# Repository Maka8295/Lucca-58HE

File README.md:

# Lucca 58HE
The Lucca 58HE is a 58 key hall effect split keyboard!

This keyboard is still very much a work in progress!! Kicad files for PCBs and switch plate, 3d files for case all available. Currently working under KMK!

## Features

- Fully addressable per-key RGB
- 10-point RGB Underglow on each half
- Full USB-C support
- Hardware support for both SPI and UART communication between halves
- OLED screens
- Rapid Trigger
- 3D Printed Case
- Compatible with standard HE Switches, I reccomend Gateron Jades

## Bill of Materials

- Multiplexer - ADG732BSUZ 
- MCU - Waveshare RP2040 Zero 
- OLED - SSD1306 128x32 
- HE Sensor - DRV5053VAQDBZR 
- LPF Resistor 1.5k Ohm 0805 package
- I2C / SPI pull-up resistor 4.7k Ohm 0805 package
- 0 Ohm Resistors for UART mode 0805 package
- Filter caps 100nF 0805 package
- SK6803 MINI-E (you can use SK6812 instead but dont use both under glow and per key as current draw is too high)
- M2.5, 3mm brass stand offs 
- M2.5, 12mm screws with flat tops
- M2.5 x 6 x 0.4mm washers 
- M2.5 nuts 1.8mm thick
- My 3d Printed case!

## How To Install

- ...

## To do

- OLED code implementation
- implement auto calibration
- QMK port
- New HE sensor?

NEW STATUS UPDATE:

Am currently typing this update from the Lucca58HE! So its fully up and running now! There is definitely a slight latency with UART on the slave half of the keyboard. The PCB supports SPI which could potentialy have latency reductions. It might also be possible to get UART latency down too, especially once im using QMK.

OLD STATUS UPDATES:

Left half of the keyboard is now perfectly functioning under KMK! changing the actuation from from 0 to 3.5mm is possible, but some weirdness means theres a deadzone towards the end of the keystroke, it can be fixed by increasing the distance between the switch plate and PCB so not a big deal. Could probably be avoided with different HE sensors?

Working with QMK has proved a lot more difficult than i thought, so im going to get it working with KMK and circuitpython first, and then worry about QMK support after!

Hall effect sensors are currently resulting in a resolution of 0.00706mm, so things are looking very promising. My choice of HE sensor results in a voltage range of ~0 to ~0.4v, so using a different HE sensor with a greater sensitivity (not to be confused with resolution) could result in even greater resolution of distance traveled, as the 12bit ADC on the RP2040 references the internal 3.3v. Am going on family holiday soon so progress will slow down a lot, may not be able to finish the project until the new year...

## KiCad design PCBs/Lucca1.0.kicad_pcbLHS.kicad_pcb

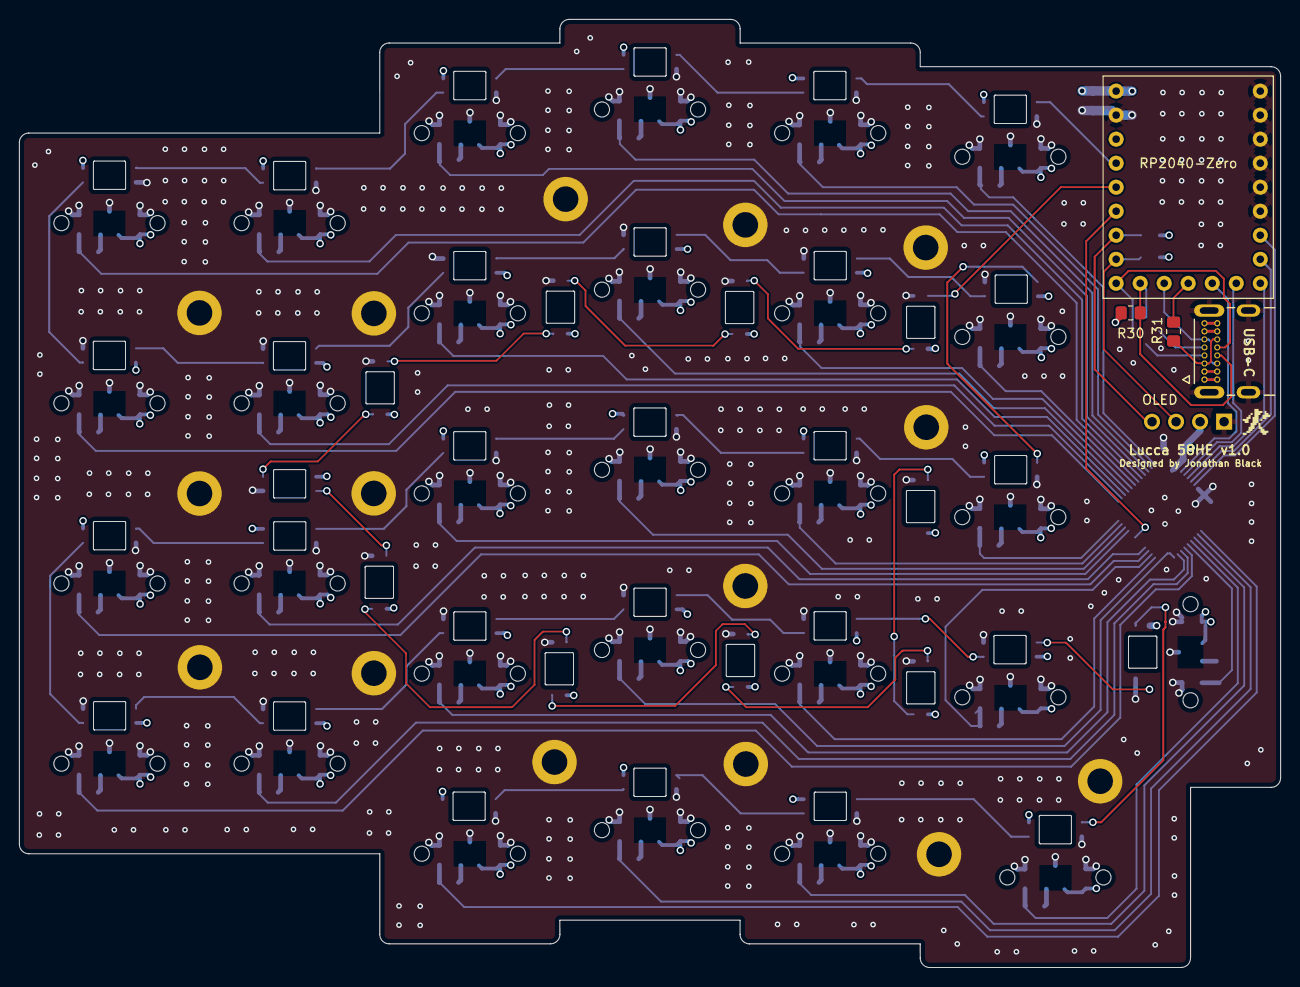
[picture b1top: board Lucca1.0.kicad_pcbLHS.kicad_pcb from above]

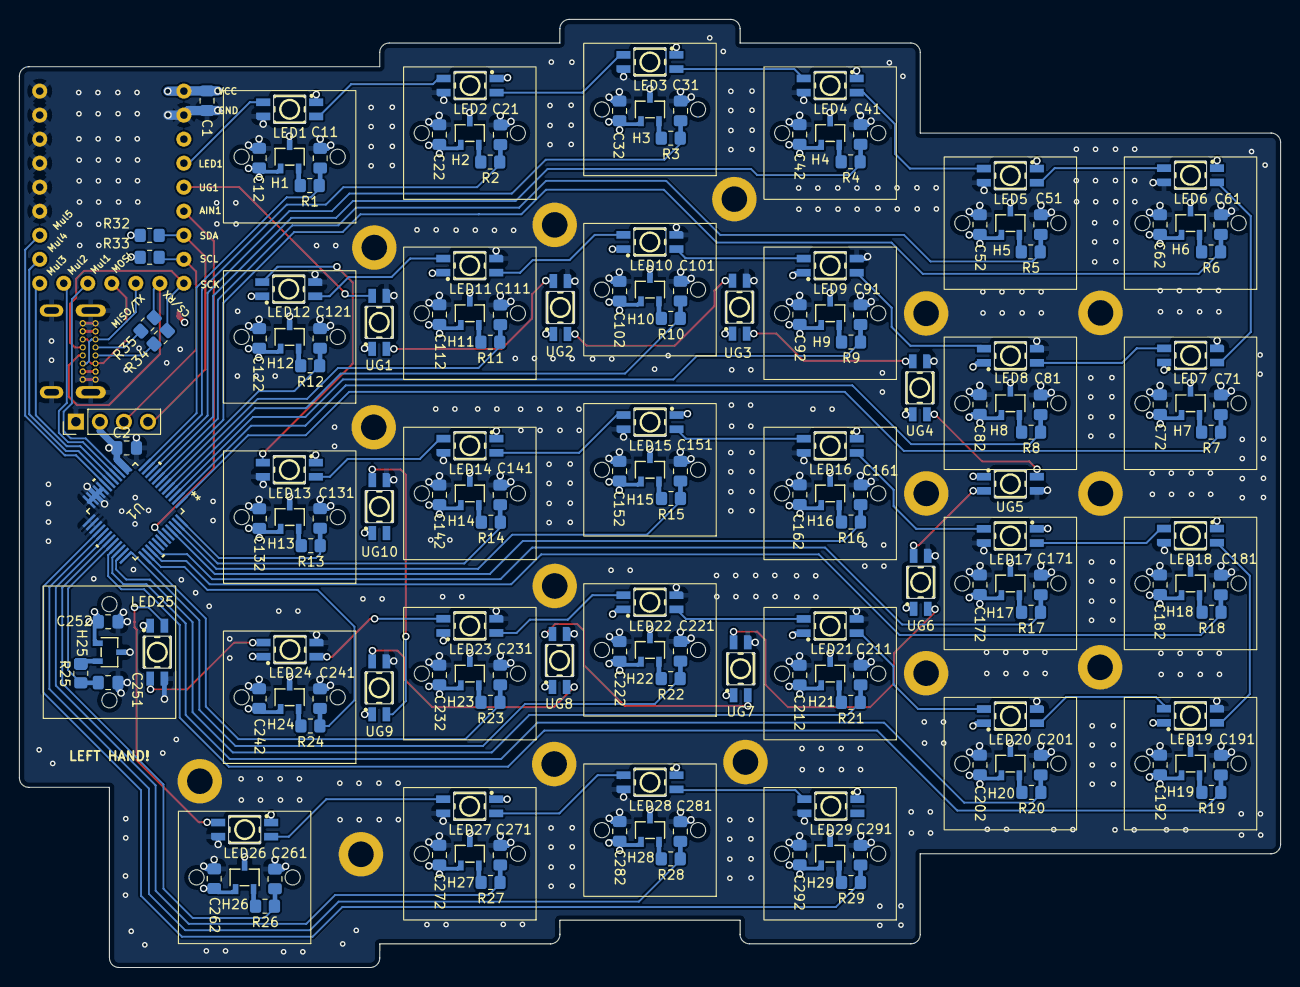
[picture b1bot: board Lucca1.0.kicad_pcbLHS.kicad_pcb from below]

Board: 4 copper layers, 133.4 x 100.2 mm, 166 parts (162 on the bottom side), 110 nets.

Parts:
C1, C2, C11, C12, C21, C22, C31, C32, C41, C42, C51, C52, C61, C62, C71, C72, C81, C82, C91, C92, C101, C102, C111, C112, C121, C122, C131, C132, C141, C142, C151, C152, C161, C162, C171, C172, C181, C182, C191, C192, C201, C202, C211, C212, C221, C222, C231, C232, C241, C242, C251, C252, C261, C262, C271, C272, C281, C282, C291, C292: C; C_0805_2012Metric_Pad1.18x1.45mm_HandSolder
H1, H2, H3, H4, H5, H6, H7, H8, H9, H10, H11, H12, H13, H14, H15, H16, H17, H18, H19, H20, H21, H22, H23, H24, H27, H28, H29: HX6659ISO-B; SOT-23-3_L2.9-W1.6-P1.90-LS2.8-BR
H25, H26: HX6659ISO-B; 1.5U Key
LED1, LED2, LED3, LED4, LED5, LED6, LED7, LED8, LED9, LED10, LED11, LED12, LED13, LED14, LED15, LED16, LED17, LED18, LED19, LED20, LED21, LED22, LED23, LED24, LED25, LED26, LED27, LED28, LED29: SK6812MINI-E_C5149201; LED-SMD_L3.2-W2.8-TR
OLED: OLED; OLEDPinHeader_1x04_P2.54mm_Vertical
R1, R2, R3, R4, R5, R6, R7, R8, R9, R10, R11, R12, R13, R14, R15, R16, R17, R18, R19, R20, R21, R22, R23, R24, R25, R26, R27, R28, R29, R30, R31, R32, R33, R34, R35: R_0805_2012Metric_Pad1.20x1.40mm_HandSolder
RP2040-Zero: RP2040-Zero; RP2040-Zero Through Hole foot print (Correct version)
U1: ADG732BSUZ; SU_48_ADI-M
UG1, UG2, UG3, UG4, UG5, UG6, UG7, UG8, UG9, UG10: SK6812MINI-E_C5149201; NONFlippedUnderGlowLED

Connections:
A1: C11.1, R1.2, U1.12 (S1)
A2: C21.1, R2.2, U1.11 (S2)
A3: C31.1, R3.2, U1.10 (S3)
A4: C41.1, R4.2, U1.9 (S4)
A5: C51.1, R5.2, U1.8 (S5)
A6: C61.1, R6.2, U1.7 (S6)
A7: C71.1, R7.2, U1.1 (S12)
A8: C81.1, R8.2, U1.2 (S11)
A9: C91.1, R9.2, U1.3 (S10)
A10: C101.1, R10.2, U1.4 (S9)
A11: C111.1, R11.2, U1.5 (S8)
A12: C121.1, R12.2, U1.6 (S7)
A13: C131.1, R13.2, U1.48 (S13)
A14: C141.1, R14.2, U1.47 (S14)
A15: C151.1, R15.2, U1.46 (S15)
A16: C161.1, R16.2, U1.45 (S16)
A17: C171.1, R17.2, U1.40 (S32)
A18: C181.1, R18.2, U1.39 (S31)
A19: C191.1, R19.2, U1.33 (S25)
A20: C201.1, R20.2, U1.34 (S26)
A21: C211.1, R21.2, U1.35 (S27)
A22: C221.1, R22.2, U1.36 (S28)
A23: C231.1, R23.2, U1.37 (S29)
A24: C241.1, R24.2, U1.38 (S30)
A25: C251.1, R25.2, U1.32 (S24)
A26: C261.1, R26.2, U1.31 (S23)
A27: C271.1, R27.2, U1.30 (S22)
A28: C281.1, R28.2, U1.29 (S21)
A29: C291.1, R29.2, U1.28 (S20)
AIN1: RP2040-Zero.18 (GPIO27), U1.43 (D)
CS: R30.2, R35.1, R35.2, RP2040-Zero.14 (GPIO13)
GND: C1.2, C2.2, C11.2, C12.1, C21.2, C22.1, C31.2, C32.1, C41.2, C42.1, C51.2, C52.1, C61.2, C62.1, C71.2, C72.1, C81.2, C82.1, C91.2, C92.1, C101.2, C102.1, C111.2, C112.1, C121.2, C122.1, C131.2, C132.1, C141.2, C142.1, C151.2, C152.1, C161.2, C162.1, C171.2, C172.1, C181.2, C182.1, C191.2, C192.1, C201.2, C202.1, C211.2, C212.1, C221.2, C222.1, C231.2, C232.1, C241.2, C242.1, C251.2, C252.1, C261.2, C262.1, C271.2, C272.1, C281.2, C282.1, C291.2, C292.1, H1.3 (GND), H2.3 (GND), H3.3 (GND), H4.3 (GND), H5.3 (GND), H6.3 (GND), H7.3 (GND), H8.3 (GND), H9.3 (GND), H10.3 (GND), H11.3 (GND), H12.3 (GND), H13.3 (GND), H14.3 (GND), H15.3 (GND), H16.3 (GND), H17.3 (GND), H18.3 (GND), H19.3 (GND), H20.3 (GND), H21.3 (GND), H22.3 (GND), H23.3 (GND), H24.3 (GND), H25.3 (GND), H26.3 (GND), H27.3 (GND), H28.3 (GND), H29.3 (GND), LED1.3 (GND), LED2.3 (GND), LED3.3 (GND), LED4.3 (GND), LED5.3 (GND), LED6.3 (GND), LED7.3 (GND), LED8.3 (GND), LED9.3 (GND), LED10.3 (GND), LED11.3 (GND), LED12.3 (GND), LED13.3 (GND), LED14.3 (GND), LED15.3 (GND), LED16.3 (GND), LED17.3 (GND), LED18.3 (GND), LED19.3 (GND), LED20.3 (GND), LED21.3 (GND), LED22.3 (GND), LED23.3 (GND), LED24.3 (GND), LED25.3 (GND), LED26.3 (GND), LED27.3 (GND), LED28.3 (GND), LED29.3 (GND), OLED.1, RP2040-Zero.1 (GPIO0), RP2040-Zero.2 (GPIO1), RP2040-Zero.3 (GPIO2), RP2040-Zero.4 (GPIO3), RP2040-Zero.5 (GPIO4), RP2040-Zero.6 (GPIO5), RP2040-Zero.22 (GND), U1.20 (CS*), U1.21 (WR*), U1.22 (EN*), U1.23 (GND), U1.24 (VSS), U1.25 (S17), U1.26 (S18), U1.27 (S19), UG1.3 (GND), UG2.3 (GND), UG3.3 (GND), UG4.3 (GND), UG5.3 (GND), UG6.3 (GND), UG7.3 (GND), UG8.3 (GND), UG9.3 (GND), UG10.3 (GND)
LED1: LED1.4 (DIN), RP2040-Zero.20 (GPIO29)
LED2: LED1.2 (DOUT), LED2.4 (DIN)
LED3: LED2.2 (DOUT), LED3.4 (DIN)
LED4: LED3.2 (DOUT), LED4.4 (DIN)
LED5: LED4.2 (DOUT), LED5.4 (DIN)
LED6: LED5.2 (DOUT), LED6.4 (DIN)
LED7: LED6.2 (DOUT), LED7.4 (DIN)
LED8: LED7.2 (DOUT), LED8.4 (DIN)
LED9: LED8.2 (DOUT), LED9.4 (DIN)
LED10: LED9.2 (DOUT), LED10.4 (DIN)
LED11: LED10.2 (DOUT), LED11.4 (DIN)
LED12: LED11.2 (DOUT), LED12.4 (DIN)
LED13: LED12.2 (DOUT), LED13.4 (DIN)
LED14: LED13.2 (DOUT), LED14.4 (DIN)
LED15: LED14.2 (DOUT), LED15.4 (DIN)
LED16: LED15.2 (DOUT), LED16.4 (DIN)
LED17: LED16.2 (DOUT), LED17.4 (DIN)
LED18: LED17.2 (DOUT), LED18.4 (DIN)
LED19: LED18.2 (DOUT), LED19.4 (DIN)
LED20: LED19.2 (DOUT), LED20.4 (DIN)
LED21: LED20.2 (DOUT), LED21.4 (DIN)
LED22: LED21.2 (DOUT), LED22.4 (DIN)
LED23: LED22.2 (DOUT), LED23.4 (DIN)
LED24: LED23.2 (DOUT), LED24.4 (DIN)
LED25: LED24.2 (DOUT), LED25.4 (DIN)
LED26: LED25.2 (DOUT), LED26.4 (DIN)
LED27: LED26.2 (DOUT), LED27.4 (DIN)
LED28: LED27.2 (DOUT), LED28.4 (DIN)
LED29: LED28.2 (DOUT), LED29.4 (DIN)
MOSI(L): R31.1, R31.2, RP2040-Zero.12 (GPIO11)
MulControl1: RP2040-Zero.11 (GPIO10), U1.15 (A0)
MulControl2: RP2040-Zero.10 (GPIO9), U1.16 (A1)
MulControl3: RP2040-Zero.9 (GPIO8), U1.17 (A2)
MulControl4: RP2040-Zero.8 (GPIO7), U1.18 (A3)
MulControl5: RP2040-Zero.7 (GPIO6), U1.19 (A4)
Q1: H1.2 (VOUT), R1.1
Q2: H2.2 (VOUT), R2.1
Q3: H3.2 (VOUT), R3.1
Q4: H4.2 (VOUT), R4.1
Q5: H5.2 (VOUT), R5.1
Q6: H6.2 (VOUT), R6.1
Q7: H7.2 (VOUT), R7.1
Q8: H8.2 (VOUT), R8.1
Q9: H9.2 (VOUT), R9.1
Q10: H10.2 (VOUT), R10.1
Q11: H11.2 (VOUT), R11.1
Q12: H12.2 (VOUT), R12.1
Q13: H13.2 (VOUT), R13.1
Q14: H14.2 (VOUT), R14.1
Q15: H15.2 (VOUT), R15.1
Q16: H16.2 (VOUT), R16.1
Q17: H17.2 (VOUT), R17.1
Q18: H18.2 (VOUT), R18.1
Q19: H19.2 (VOUT), R19.1
Q20: H20.2 (VOUT), R20.1
Q21: H21.2 (VOUT), R21.1
Q22: H22.2 (VOUT), R22.1
Q23: H23.2 (VOUT), R23.1
Q24: H24.2 (VOUT), R24.1
Q25: H25.2 (VOUT), R25.1
Q26: H26.2 (VOUT), R26.1
Q27: H27.2 (VOUT), R27.1
Q28: H28.2 (VOUT), R28.1
Q29: H29.2 (VOUT), R29.1
SCK: R34.1, R34.2, RP2040-Zero.15 (GPIO14)
SCL: OLED.3, R33.2, RP2040-Zero.16 (GPIO15)
SDA: OLED.4, R32.2, RP2040-Zero.17 (GPIO26)
UGLED1: RP2040-Zero.19 (GPIO28), UG1.4 (DIN)
UGLED2: UG1.2 (DOUT), UG2.4 (DIN)
UGLED3: UG2.2 (DOUT), UG3.4 (DIN)
UGLED4: UG3.2 (DOUT), UG4.4 (DIN)
UGLED5: UG4.2 (DOUT), UG5.4 (DIN)
UGLED6: UG5.2 (DOUT), UG6.4 (DIN)
UGLED7: UG6.2 (DOUT), UG7.4 (DIN)
UGLED8: UG7.2 (DOUT), UG8.4 (DIN)
UGLED9: UG8.2 (DOUT), UG9.4 (DIN)
UGLED10: UG9.2 (DOUT), UG10.4 (DIN)
VCC: C1.1, C2.1, C12.2, C22.2, C32.2, C42.2, C52.2, C62.2, C72.2, C82.2, C92.2, C102.2, C112.2, C122.2, C132.2, C142.2, C152.2, C162.2, C172.2, C182.2, C192.2, C202.2, C212.2, C222.2, C232.2, C242.2, C252.2, C262.2, C272.2, C282.2, C292.2, H1.1 (VDD), H2.1 (VDD), H3.1 (VDD), H4.1 (VDD), H5.1 (VDD), H6.1 (VDD), H7.1 (VDD), H8.1 (VDD), H9.1 (VDD), H10.1 (VDD), H11.1 (VDD), H12.1 (VDD), H13.1 (VDD), H14.1 (VDD), H15.1 (VDD), H16.1 (VDD), H17.1 (VDD), H18.1 (VDD), H19.1 (VDD), H20.1 (VDD), H21.1 (VDD), H22.1 (VDD), H23.1 (VDD), H24.1 (VDD), H25.1 (VDD), H26.1 (VDD), H27.1 (VDD), H28.1 (VDD), H29.1 (VDD), LED1.1 (VDD), LED2.1 (VDD), LED3.1 (VDD), LED4.1 (VDD), LED5.1 (VDD), LED6.1 (VDD), LED7.1 (VDD), LED8.1 (VDD), LED9.1 (VDD), LED10.1 (VDD), LED11.1 (VDD), LED12.1 (VDD), LED13.1 (VDD), LED14.1 (VDD), LED15.1 (VDD), LED16.1 (VDD), LED17.1 (VDD), LED18.1 (VDD), LED19.1 (VDD), LED20.1 (VDD), LED21.1 (VDD), LED22.1 (VDD), LED23.1 (VDD), LED24.1 (VDD), LED25.1 (VDD), LED26.1 (VDD), LED27.1 (VDD), LED28.1 (VDD), LED29.1 (VDD), OLED.2, R30.1, R32.1, R33.1, RP2040-Zero.23 (5v), U1.13 (VDD), U1.14 (VDD), UG1.1 (VDD), UG2.1 (VDD), UG3.1 (VDD), UG4.1 (VDD), UG5.1 (VDD), UG6.1 (VDD), UG7.1 (VDD), UG8.1 (VDD), UG9.1 (VDD), UG10.1 (VDD)

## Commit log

2024-06-27 Callibration for left half
2024-06-27 read me update
2024-06-27 Fixed pin assignments and added RHS callibration
2024-06-27 readme
2024-07-08 readme status update
2024-07-24 working!
2024-07-26 read me
2024-08-02 KMK Release
